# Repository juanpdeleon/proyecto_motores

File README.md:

## proyecto_motores
Analisis  por vibracion y temperatura de motores de corriente alterna de codigo abierto.
Trabajo de conclusion de curso, del Posgrado en Robotica e Inteligencia Artifical - UTEC - FURGS 2019-2021

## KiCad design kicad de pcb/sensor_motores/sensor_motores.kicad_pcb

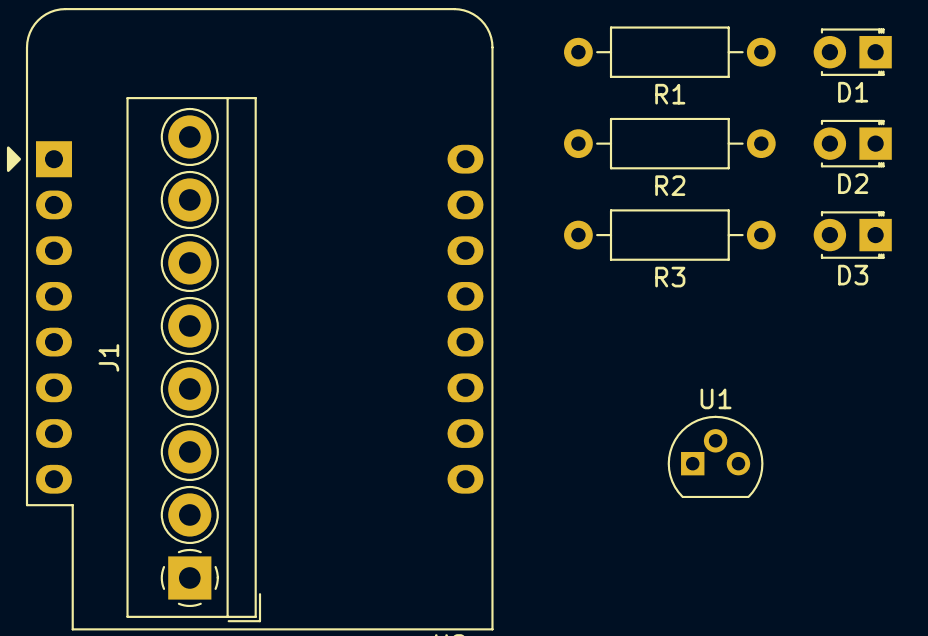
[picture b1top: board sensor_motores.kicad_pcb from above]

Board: 2 copper layers, 9 parts (0 on the bottom side), 11 nets, no tracks yet.

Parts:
D1, D2, D3: LED; LED_D1.8mm_W3.3mm_H2.4mm
J1: MPU-6050; TerminalBlock_4Ucon_1x08_P3.50mm_Horizontal
R1, R2, R3: R; R_Axial_DIN0207_L6.3mm_D2.5mm_P10.16mm_Horizontal
U1: LM35-LP; TO-92
U2: WeMos_D1_mini; WEMOS_D1_mini_light

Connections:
unnamed: D1.1, D2.1, D3.1, J1.2, U1.3, U2.10
unnamed: D1.2, R1.1
unnamed: D2.2, R2.1
unnamed: D3.2, R3.1
unnamed: J1.1, U1.1, U2.9
unnamed: J1.3, U2.14
unnamed: J1.4, U2.13
unnamed: R1.2, U2.3
unnamed: R2.2, U2.4
unnamed: R3.2, U2.5
unnamed: U1.2, U2.2

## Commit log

2022-01-25 Proyecto motores - Postrado PRIA
